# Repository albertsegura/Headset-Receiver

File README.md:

Headset-Receiver
================

Custom embedded Arduino board that provides Bluetooth/FM/Jack for a Headphones.
* Bluetooth rn-52 module
* Si4703 FM chip
* Arduino Pro mini 3.3v based board

Repository Contents
-------------------
* **/Eagle Files** - Eagle files for the two boards (.brd, .sch)

OSH PARK
--------
[  
 *Main board*](http://oshpark.com/shared_projects/1vYQ7i1L)

[  
 *Bluetooth Module*](http://oshpark.com/shared_projects/EPMXIzBB)

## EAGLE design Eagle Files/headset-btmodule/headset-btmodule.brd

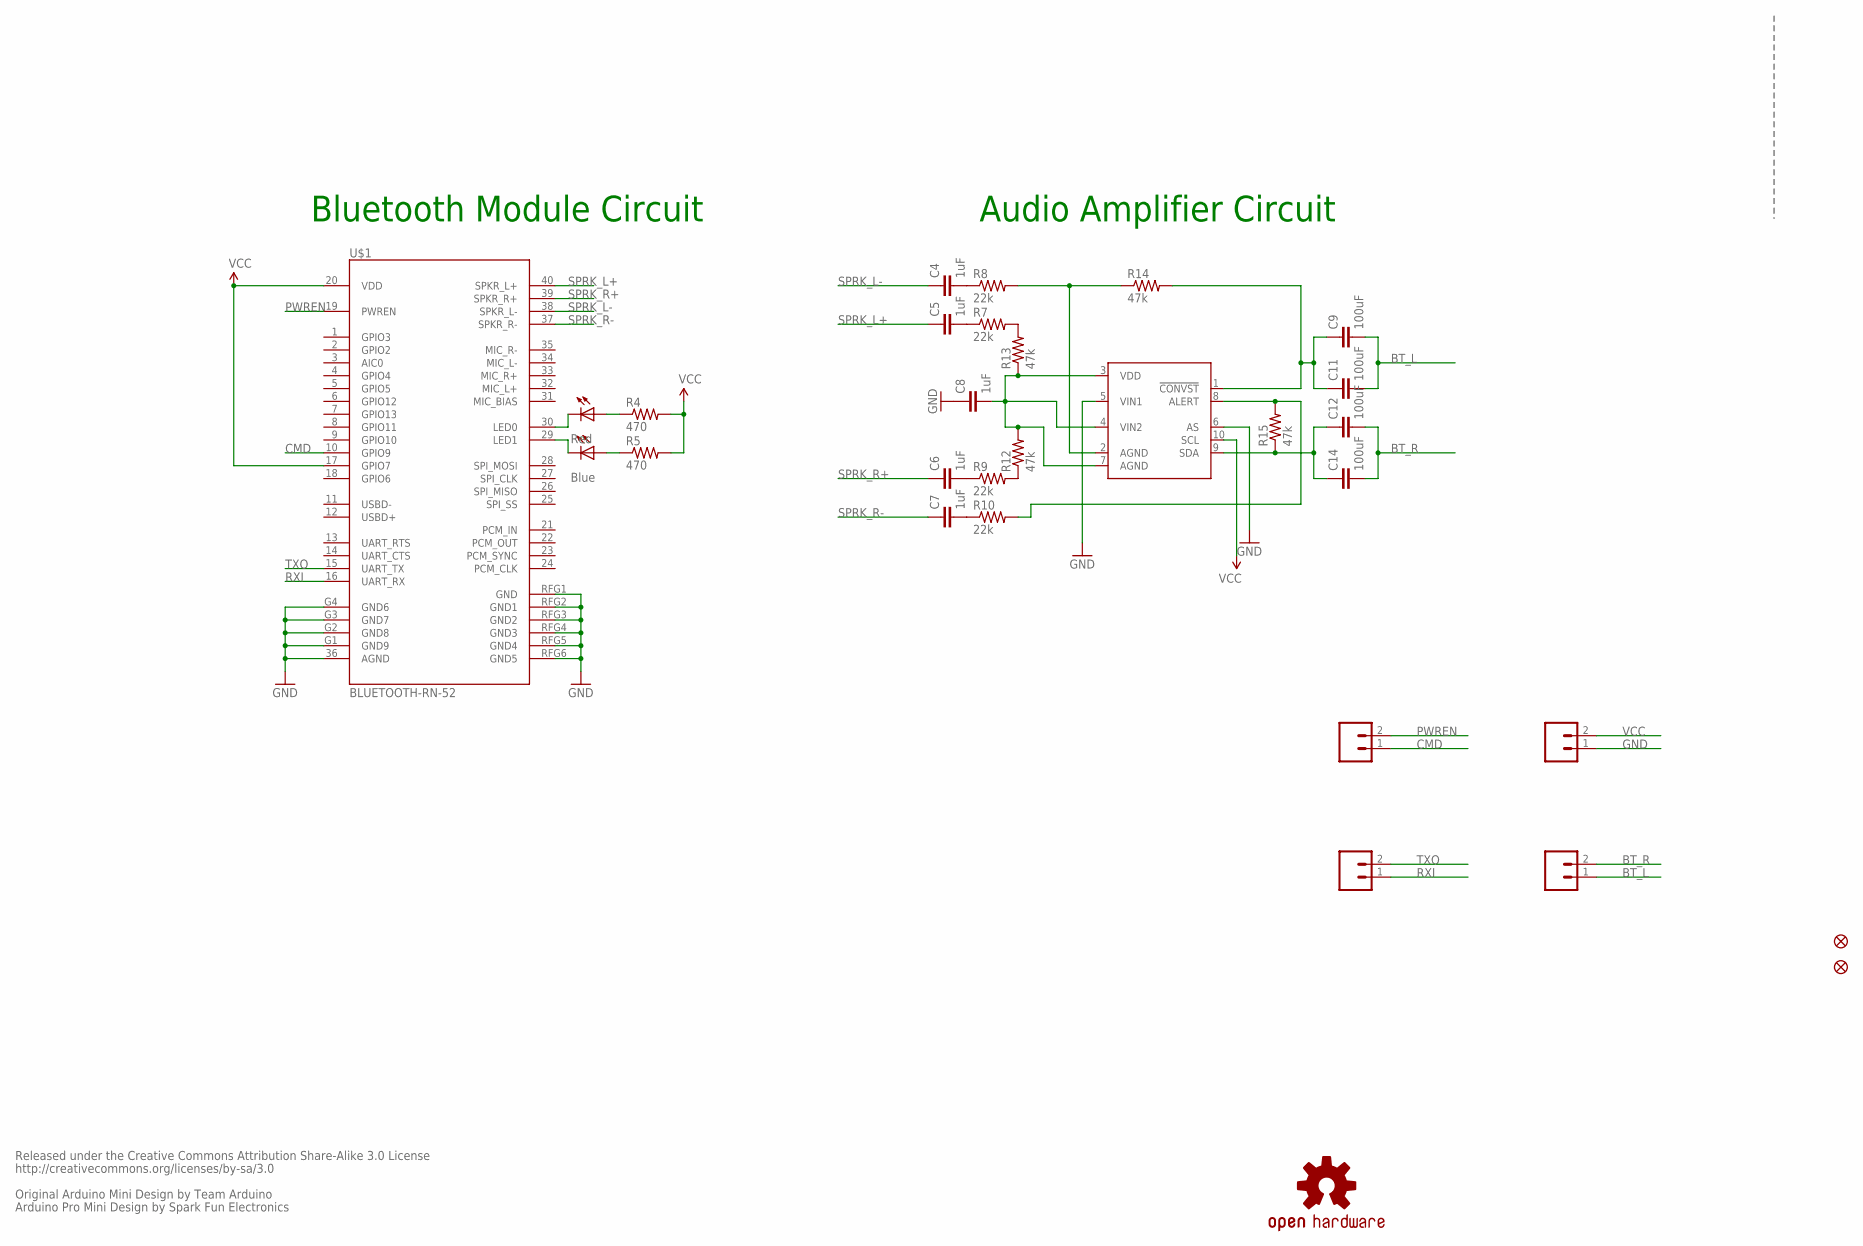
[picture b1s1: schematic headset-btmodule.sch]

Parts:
AUDIO: M02PTH; 1X02
C4, C5, C6, C7, C8: 1uF; 0402-CAP
C9, C11, C12, C14: 100uF; 0805
CMD: M02PTH; 1X02
JP5, JP8: FIDUCIALUFIDUCIAL; MICRO-FIDUCIAL
LED3: Red; LED3MM-NS
LED4: Blue; LED3MM-NS
POWER: M02PTH; 1X02
R4, R5: 470; 0402-RES
R7, R8, R9, R10: 22k; 0402-RES
R12, R13, R14, R15: 47k; 0402-RES
T: AD7992; MSOP10
TX: M02PTH; 1X02
U$1: BLUETOOTH-RN-52; RN-52
U$3: OSHW-LOGOS; OSHW-LOGO-S

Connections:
BT_L: AUDIO.1, C9.2, C11.2
BT_R: AUDIO.2, C12.2, C14.2
CMD: CMD.1, U$1.10 (GPIO9)
GND: C8.1, POWER.1, T.5 (VIN1), T.6 (AS), U$1.36 (AGND), U$1.G1 (GND9), U$1.G2 (GND8), U$1.G3 (GND7), U$1.G4 (GND6), U$1.RFG1 (GND), U$1.RFG2 (GND1), U$1.RFG3 (GND2), U$1.RFG4 (GND3), U$1.RFG5 (GND4), U$1.RFG6 (GND5)
unnamed: LED3.A, R4.1
unnamed: LED4.A, R5.1
unnamed: LED3.K (C), U$1.30 (LED0)
unnamed: LED4.K (C), U$1.29 (LED1)
unnamed: C12.1, C14.1, R15.1, T.9 (SDA)
unnamed: R10.2, R15.2, T.8 (ALERT)
unnamed: R7.2, R13.2
unnamed: C9.1, C11.1, R14.2, T.1 (!CONVST)
unnamed: R9.2, R12.1
unnamed: C6.2, R9.1
unnamed: C7.2, R10.1
unnamed: C5.2, R7.1
unnamed: C4.2, R8.1
unnamed: C8.2, R12.2, R13.1, T.3 (VDD), T.4 (VIN2), T.7 (AGND)
unnamed: R8.2, R14.1, T.2 (AGND)
PWREN: CMD.2, U$1.19 (PWREN)
RXI: TX.1, U$1.16 (UART_RX)
SPRK_L+: C5.1, U$1.40 (SPKR_L+)
SPRK_L-: C4.1, U$1.38 (SPKR_L-)
SPRK_R+: C6.1, U$1.39 (SPKR_R+)
SPRK_R-: C7.1, U$1.37 (SPKR_R-)
TXO: TX.2, U$1.15 (UART_TX)
VCC: POWER.2, R4.2, R5.2, T.10 (SCL), U$1.17 (GPIO7), U$1.20 (VDD)

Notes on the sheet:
Released under the Creative Commons Attribution Share-Alike 3.0 License
http://creativecommons.org/licenses/by-sa/3.0
Original Arduino Mini Design by Team Arduino
Arduino Pro Mini Design by Spark Fun Electronics
Bluetooth Module Circuit
Audio Amplifier Circuit

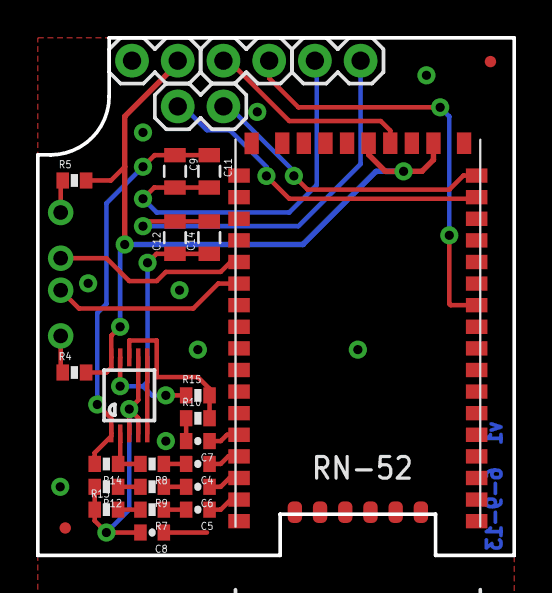
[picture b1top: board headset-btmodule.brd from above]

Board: 2 copper layers, 26.5 x 28.8 mm, 30 parts (1 on the bottom side), 27 nets.

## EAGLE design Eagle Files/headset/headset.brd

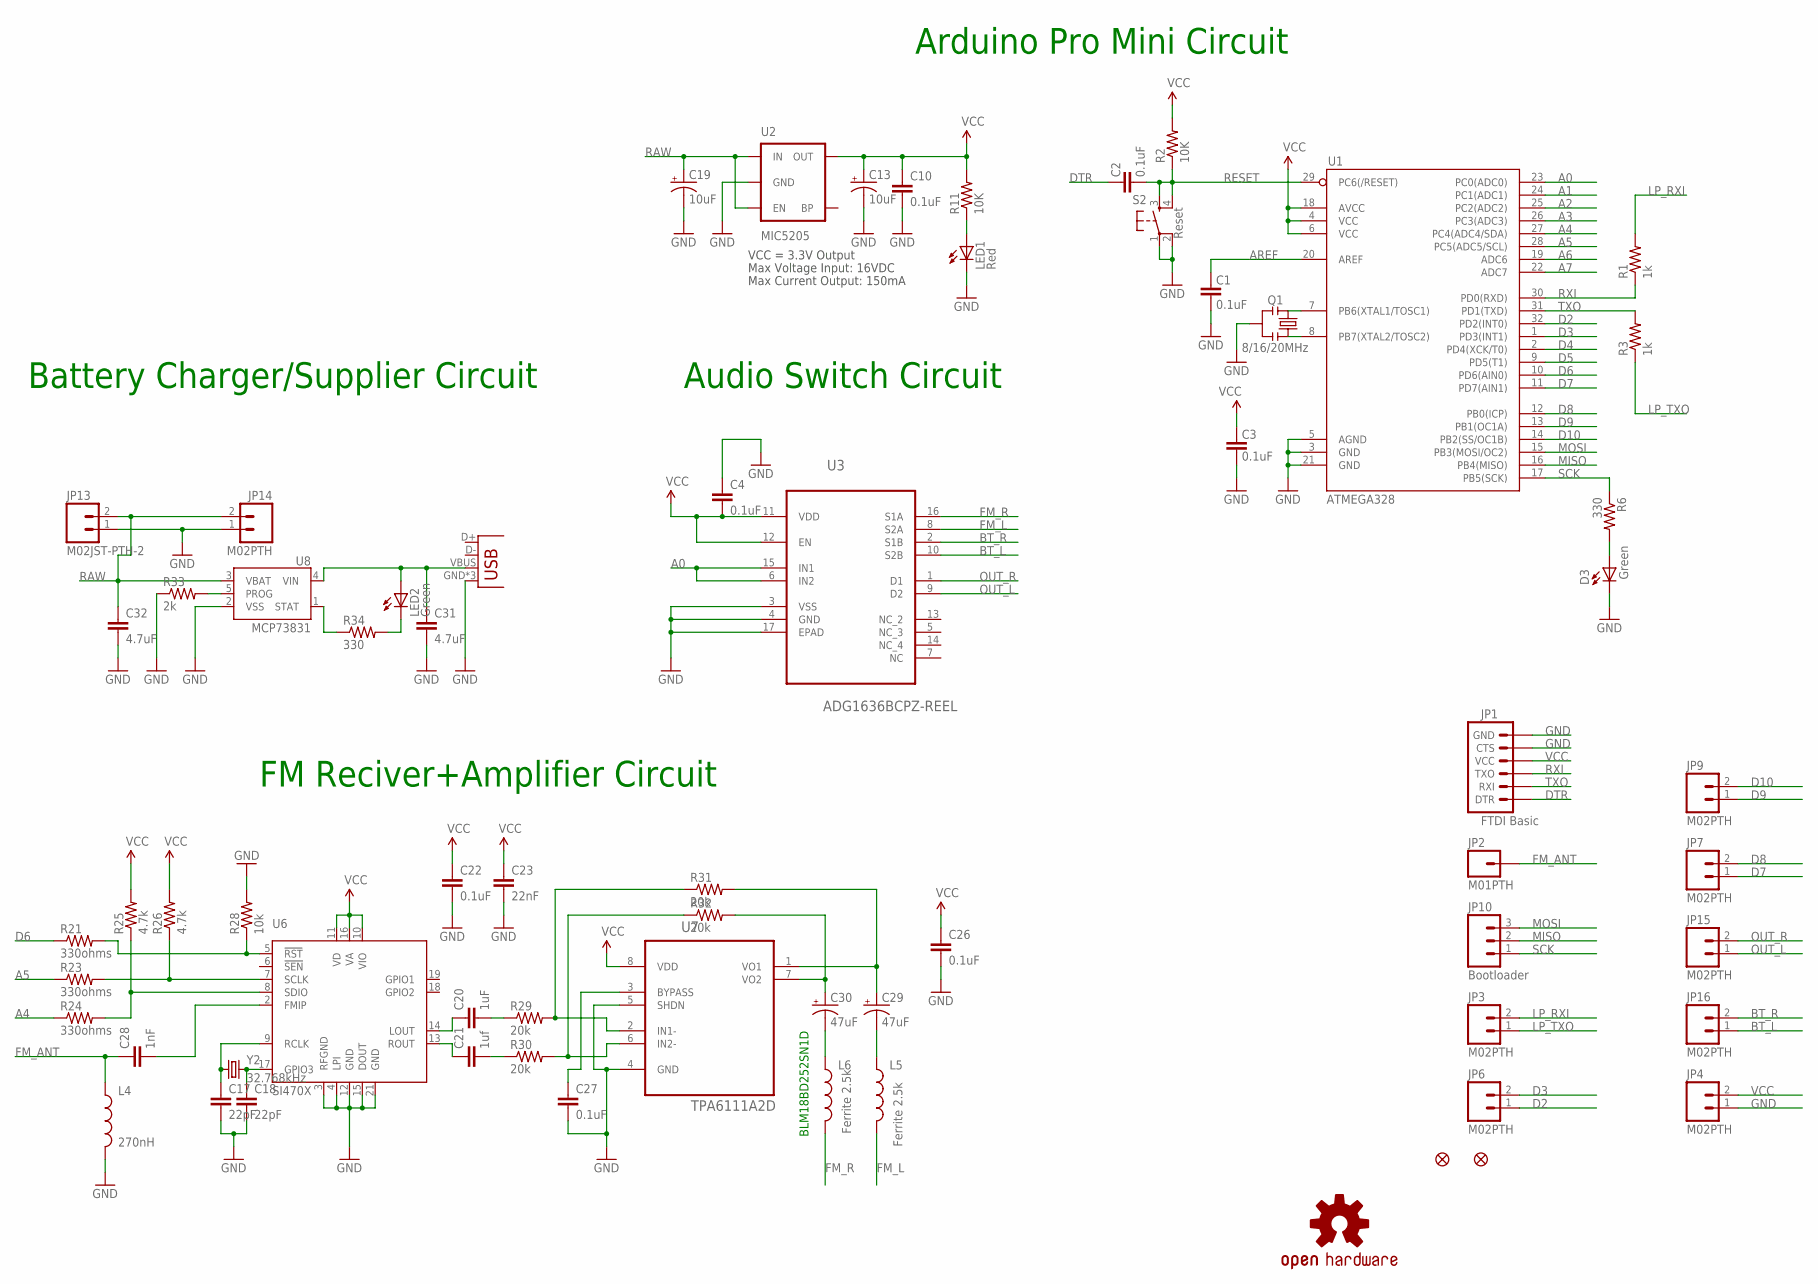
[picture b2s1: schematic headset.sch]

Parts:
C1, C2, C3, C4, C10, C22, C26, C27: 0.1uF; 0402-CAP
C13, C19: 10uF; EIA3216
C17, C18: 22pF; 0402-CAP
C20: 1uF; 0402-CAP
C21: 1uf; 0402-CAP
C23: 22nF; 0402-CAP
C28: 1nF; 0402-CAP
C29, C30: 47uF; EIA3528
C31, C32: 4.7uF; 0402-CAP
D3: Green; LED-0603
JP1: FTDI Basic; 1X06
JP2: M01PTH; 1X01
JP3, JP4, JP6, JP7, JP9, JP14, JP15, JP16: M02PTH; 1X02
JP5, JP8: FIDUCIALUFIDUCIAL; MICRO-FIDUCIAL
JP10: Bootloader; 1X03
JP12: USB-MICROB
JP13: M02JST-PTH-2; JST-2-PTH
L4: 270nH; C0402
L5, L6: Ferrite 2.5k; C0402
LED1: Red; LED-0603
LED2: Green; LED3MM-NS
Q1: 8/16/20MHz; RESONATOR-SMD
R1, R3: 1k; 0402-RES
R2, R11: 10K; 0402-RES
R6, R34: 330; 0402-RES
R21, R23, R24: 330ohms; 0402-RES
R25, R26: 4.7k; 0402-RES
R28: 10k; 0402-RES
R29, R30, R31, R32: 20k; 0402-RES
R33: 2k; 0402-RES
S2: Reset; TACTILE_SWITCH_SMD
U1: ATMEGA328; TQFP32-08
U2: MIC5205; SOT23-5
U3: ADG1636BCPZ-REEL; QFN65P400X400X100-17N
U6: SI470X
U7: TPA6111A2D; SOIC127P600X175-8N
U8: MCP73831; SOT23-5
U$3: OSHW-LOGOS; OSHW-LOGO-S
Y2: 32.768kHz; CRYSTAL-32KHZ-SMD

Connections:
A0: U1.23 (PC0(ADC0)), U3.6 (IN2), U3.15 (IN1)
A1: U1.24 (PC1(ADC1))
A2: U1.25 (PC2(ADC2))
A3: U1.26 (PC3(ADC3))
A4: R24.1, U1.27 (PC4(ADC4/SDA))
A5: R23.1, U1.28 (PC5(ADC5/SCL))
A6: U1.19 (ADC6)
A7: U1.22 (ADC7)
AREF: C1.2, U1.20 (AREF)
BT_L: JP16.1, U3.10 (S2B)
BT_R: JP16.2, U3.2 (S1B)
D2: JP6.1, U1.32 (PD2(INT0))
D3: JP6.2, U1.1 (PD3(INT1))
D4: U1.2 (PD4(XCK/T0))
D5: U1.9 (PD5(T1))
D6: R21.1, U1.10 (PD6(AIN0))
D7: JP7.1, U1.11 (PD7(AIN1))
D8: JP7.2, U1.12 (PB0(ICP))
D9: JP9.1, U1.13 (PB1(OC1A))
D10: JP9.2, U1.14 (PB2(SS/OC1B))
DTR: C2.2, JP1.1 (DTR)
FM_ANT: C28.1, JP2.1, L4.1
FM_L: L5.2, U3.8 (S2A)
FM_R: L6.2, U3.16 (S1A)
GND: C1.1, C3.1, C4.1, C10.2, C13.C (-), C17.2, C18.2, C19.C (-), C22.2, C23.2, C26.2, C27.2, C31.2, C32.2, D3.C, JP1.5 (CTS), JP1.6 (GND), JP4.1, JP12.GND, JP12.MT1 (GND), JP12.MT2 (GND), JP13.1, JP14.1, L4.2, LED1.C, Q1.2, R28.2, R33.1, S2.1, S2.2, U1.3 (GND), U1.5 (AGND), U1.21 (GND), U2.2 (GND), U3.3 (VSS), U3.4 (GND), U3.17 (EPAD), U6.3 (RFGND), U6.4 (LPI), U6.12 (GND), U6.15 (DOUT), U6.21 (GND), U7.4 (GND), U7.5 (SHDN), U8.2 (VSS)
LP_RXI: JP3.2, R1.2
LP_TXO: JP3.1, R3.1
MISO: JP10.2, U1.16 (PB4(MISO))
MOSI: JP10.3, U1.15 (PB3(MOSI/OC2))
unnamed: Q1.1, U1.8 (PB7(XTAL2/TOSC2))
unnamed: Q1.3, U1.7 (PB6(XTAL1/TOSC1))
unnamed: D3.A, R6.2
unnamed: R21.2, R28.1, U6.5 (!RST)
unnamed: R23.2, R26.1, U6.7 (SCLK)
unnamed: R24.2, R25.1, U6.8 (SDIO)
unnamed: C28.2, U6.2 (FMIP)
unnamed: C20.1, U6.14 (LOUT)
unnamed: C20.2, R29.1
unnamed: R29.2, R31.1, U7.2 (IN1-)
unnamed: R30.2, R32.1, U7.6 (IN2-)
unnamed: C21.2, R30.1
unnamed: C21.1, U6.13 (ROUT)
unnamed: C27.1, U7.3 (BYPASS)
unnamed: LED1.A, R11.1
unnamed: C29.A (+), R31.2, U7.1 (VO1)
unnamed: C30.A (+), R32.2, U7.7 (VO2)
unnamed: C17.1, U6.9 (RCLK), Y2.X1 (1)
unnamed: C18.1, U6.17 (GPIO3), Y2.X2 (2)
unnamed: C29.C (-), L5.1
unnamed: C30.C (-), L6.1
unnamed: C31.1, JP12.VBUS, LED2.A, U8.4 (VIN)
unnamed: LED2.K (C), R34.2
unnamed: R34.1, U8.1 (STAT)
unnamed: R33.2, U8.5 (PROG)
OUT_L: JP15.1, U3.9 (D2)
OUT_R: JP15.2, U3.1 (D1)
RAW: C19.A (+), C32.1, JP13.2, JP14.2, U2.1 (IN), U2.3 (EN), U8.3 (VBAT)
RESET: C2.1, R2.1, S2.3, S2.4, U1.29 (PC6(/RESET))
RXI: JP1.3 (TXO), R1.1, U1.30 (PD0(RXD))
SCK: JP10.1, R6.1, U1.17 (PB5(SCK))
TXO: JP1.2 (RXI), R3.2, U1.31 (PD1(TXD))
VCC: C3.2, C4.2, C10.1, C13.A (+), C22.1, C23.1, C26.1, JP1.4 (VCC), JP4.2, R2.2, R11.2, R25.2, R26.2, U1.4 (VCC), U1.6 (VCC), U1.18 (AVCC), U2.5 (OUT), U3.11 (VDD), U3.12 (EN), U6.10 (VIO), U6.11 (VD), U6.16 (VA), U7.8 (VDD)

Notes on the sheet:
Max Voltage Input: 16VDC
Max Current Output: 150mA
VCC = 3.3V Output
BLM18BD252SN1D
FM Reciver+Amplifier Circuit
Battery Charger/Supplier Circuit
Audio Switch Circuit
Arduino Pro Mini Circuit

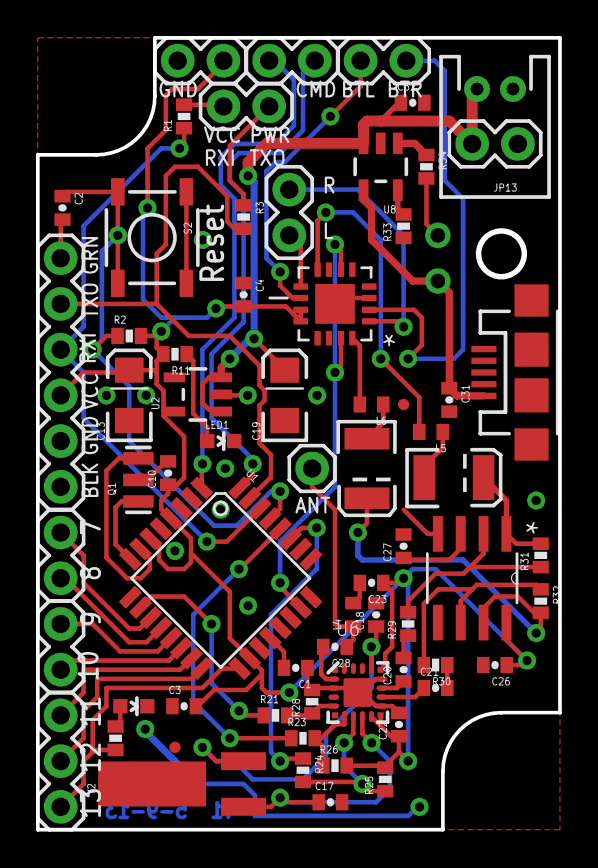
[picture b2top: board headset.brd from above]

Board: 2 copper layers, 28.9 x 43.9 mm, 68 parts (1 on the bottom side), 55 nets.

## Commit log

2013-10-04 second commit, github setup
2013-10-04 second commit, github setup 2
2013-10-04 second commit, github setup3
2013-10-04 second commit, github setup4
2013-10-04 second commit, github setup5

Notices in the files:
parts and their libraries:
SparkFun-Connectors: Licensing: CC v3.0 Share-Alike You are welcome to use this library for commercial purposes.
